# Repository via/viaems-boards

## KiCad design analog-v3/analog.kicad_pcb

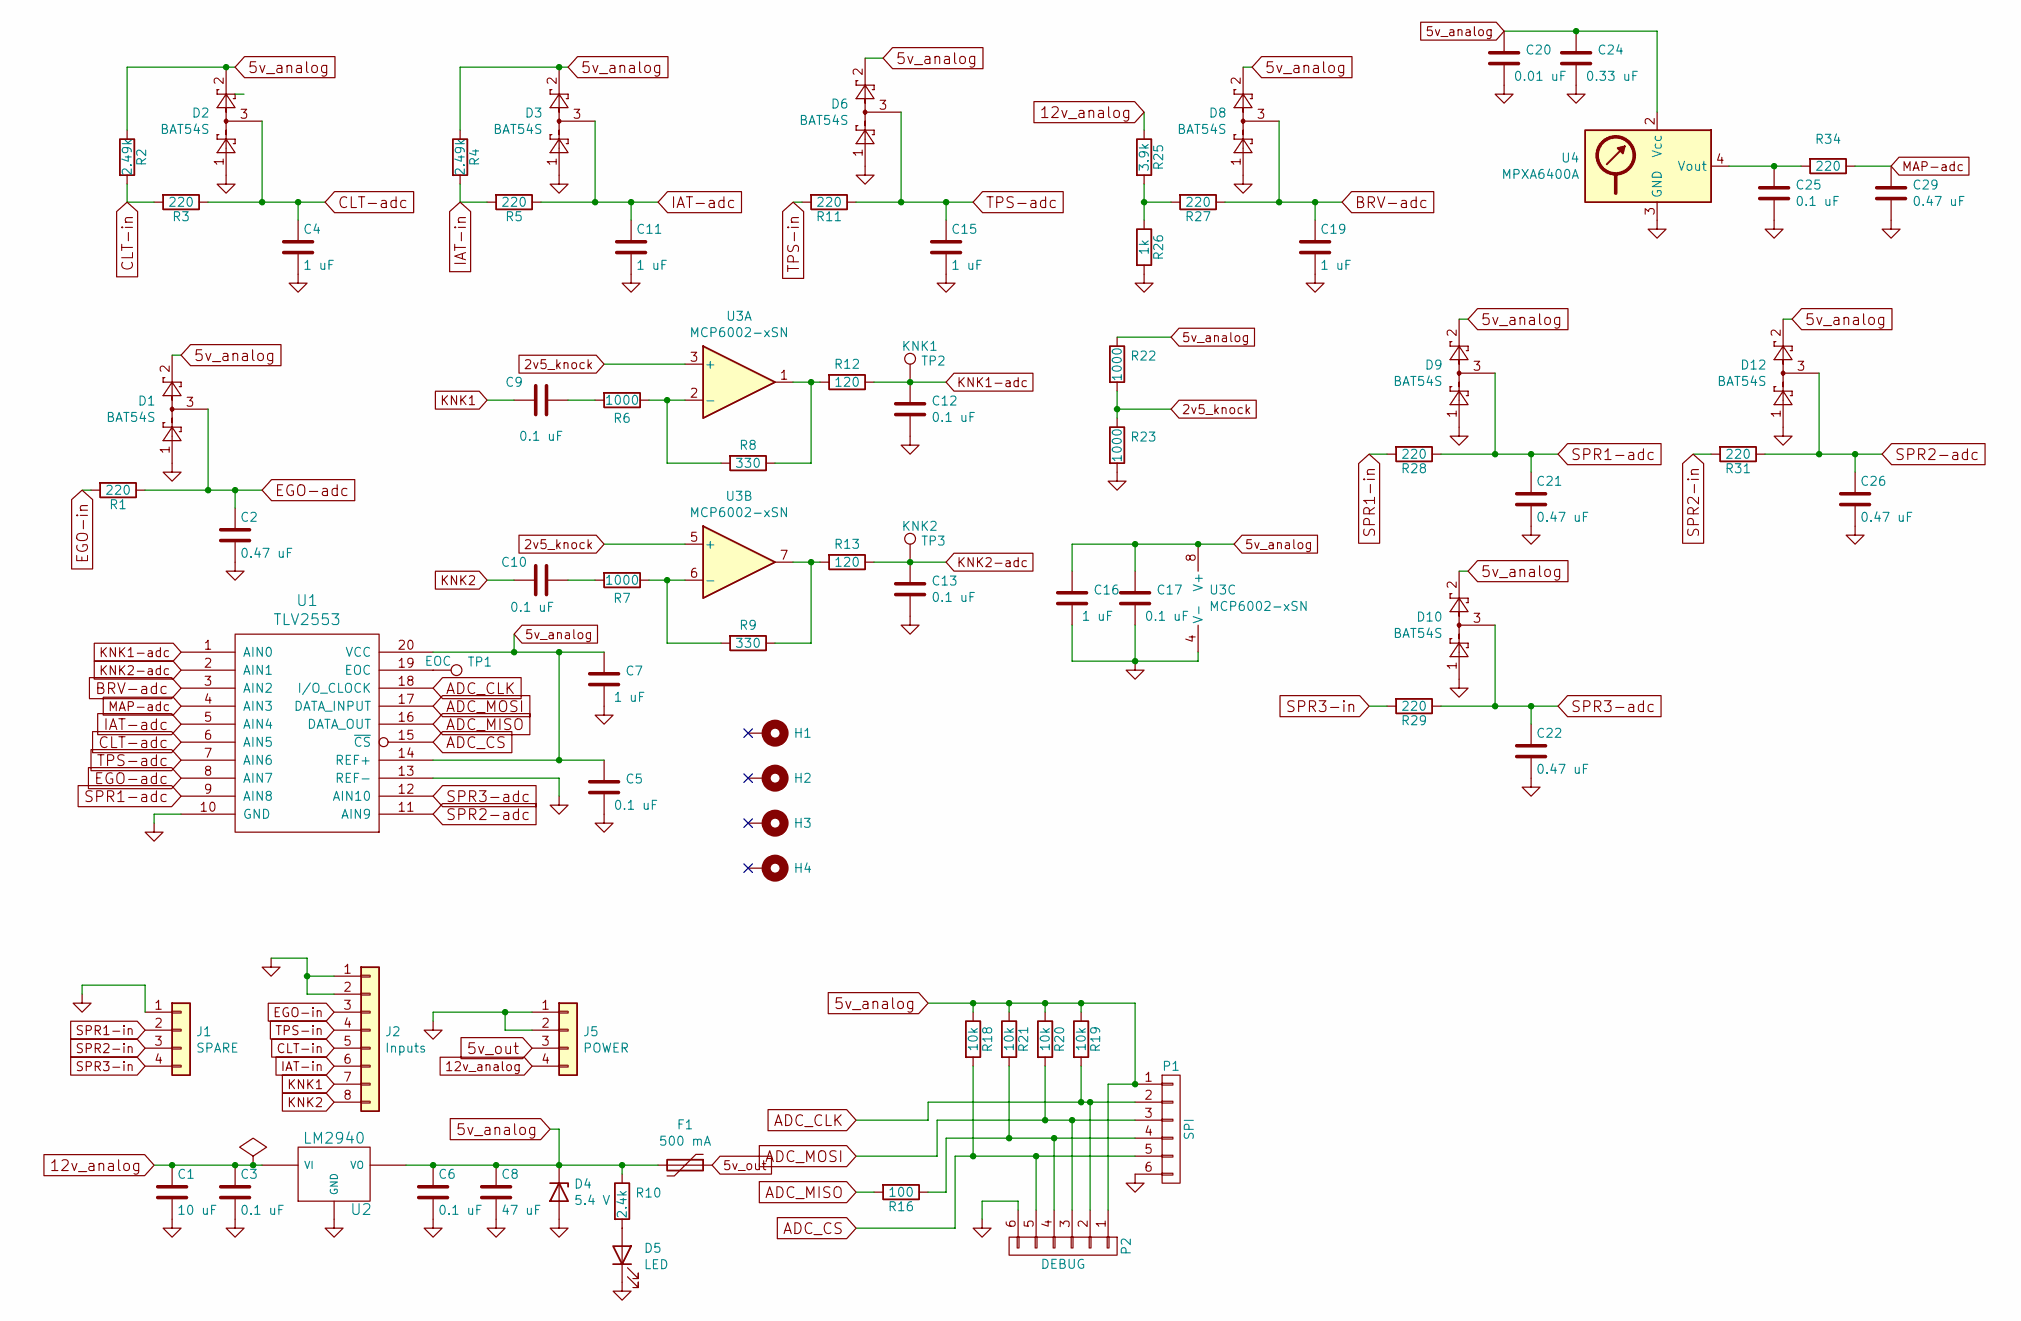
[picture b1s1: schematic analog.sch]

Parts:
C1: 10 uF; C_0805_2012Metric_Pad1.18x1.45mm_HandSolder; Rating 35V Tantalum
C2, C21, C22, C26, C29: 0.47 uF; C_0805_2012Metric_Pad1.18x1.45mm_HandSolder
C3, C5, C6, C9, C10, C12, C13, C17, C25: 0.1 uF; C_0805_2012Metric_Pad1.18x1.45mm_HandSolder
C4, C7, C11, C15, C16, C19: 1 uF; C_0805_2012Metric_Pad1.18x1.45mm_HandSolder
C8: 47 uF; C_1206_3216Metric_Pad1.33x1.80mm_HandSolder; Rating 10 V Tantalum
C20: 0.01 uF; C_0805_2012Metric_Pad1.18x1.45mm_HandSolder
C24: 0.33 uF; C_0805_2012Metric_Pad1.18x1.45mm_HandSolder
D1, D2, D3, D6, D8, D9, D10, D12: BAT54S; SOT-23
D4: 5.4 V; D_A-405_P2.54mm_Vertical_AnodeUp
D5: LED; LED_0805_2012Metric_Pad1.15x1.40mm_HandSolder
F1: 500 mA; Fuse_1206_3216Metric_Pad1.42x1.75mm_HandSolder
H1, H2, H3, H4: MountingHole_Pad; MountingHole_3mm_Pad
J1: SPARE; PinHeader_1x04_P2.54mm_Vertical
J2: Inputs; PinHeader_1x08_P2.54mm_Vertical
J5: POWER; PinHeader_1x04_P2.54mm_Vertical
P1: SPI; PinHeader_1x06_P2.54mm_Vertical
P2: DEBUG; PinHeader_1x06_P2.54mm_Vertical
R1, R3, R5, R11, R27, R28, R29, R31, R34: 220; R_0805_2012Metric_Pad1.20x1.40mm_HandSolder
R2, R4: 2.49k; R_0805_2012Metric_Pad1.20x1.40mm_HandSolder; Rating 0.1%
R6, R7, R22, R23: 1000; R_0805_2012Metric_Pad1.20x1.40mm_HandSolder
R8, R9: 330; R_0805_2012Metric_Pad1.20x1.40mm_HandSolder
R10: 2.4k; R_0805_2012Metric_Pad1.20x1.40mm_HandSolder
R12, R13: 120; R_0805_2012Metric_Pad1.20x1.40mm_HandSolder
R16: 100; R_0805_2012Metric_Pad1.20x1.40mm_HandSolder
R18, R19, R20, R21: 10k; R_0805_2012Metric_Pad1.20x1.40mm_HandSolder
R25: 3.9k; R_0805_2012Metric_Pad1.20x1.40mm_HandSolder; Rating 0.1%
R26: 1k; R_0805_2012Metric_Pad1.20x1.40mm_HandSolder; Rating 0.1%
TP1: EOC; TestPoint_THTPad_1.0x1.0mm_Drill0.5mm
TP2: KNK1; TestPoint_THTPad_1.0x1.0mm_Drill0.5mm
TP3: KNK2; TestPoint_THTPad_1.0x1.0mm_Drill0.5mm
U1: TLV2553; SOIC-20W_7.5x12.8mm_P1.27mm
U2: LM2940; TO-220-3_Horizontal_TabDown
U3: MCP6002-xSN; MSOP-8_3x3mm_P0.65mm
U4: MPXA6400A; Freescale_98ARH99089A

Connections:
2v5_knock: R22.2, R23.1, U3.3 (+), U3.5 (+)
5v_analog: C5.1, C6.1, C7.1, C8.1, C16.1, C17.1, C20.1, C24.1, D1.2, D2.2, D3.2, D4.1 (K), D6.2, D8.2, D9.2, D10.2, D12.2, F1.2, P1.1, P2.1, R2.1, R4.1, R10.1, R18.1, R19.1, R20.1, R21.1, R22.1, U1.14 (REF+), U1.20 (VCC), U2.3 (VO), U3.8 (V+), U4.2 (Vcc)
5v_out: F1.1, J5.3
12v_analog: C1.1, C3.1, J5.4, R25.1, U2.1 (VI)
ADC_CLK: P1.2, P2.2, R19.2, U1.18 (I/O_CLOCK)
ADC_CS: P1.5, P2.5, R18.2, U1.15 (~CS)
ADC_MISO: R16.2, U1.16 (DATA_OUT)
ADC_MOSI: P1.3, P2.3, R20.2, U1.17 (DATA_INPUT)
BRV-adc: C19.1, D8.3, R27.1, U1.3 (AIN2)
CLT-adc: C4.1, D2.3, R3.1, U1.6 (AIN5)
CLT-in: J2.5, R2.2, R3.2
EGO-adc: C2.1, D1.3, R1.1, U1.8 (AIN7)
EGO-in: J2.3, R1.2
GND: C1.2, C2.2, C3.2, C4.2, C5.2, C6.2, C7.2, C8.2, C11.2, C12.2, C13.2, C15.2, C16.2, C17.2, C19.2, C20.2, C21.2, C22.2, C24.2, C25.2, C26.2, C29.2, D1.1, D2.1, D3.1, D4.2 (A), D5.1 (K), D6.1, D8.1, D9.1, D10.1, D12.1, J1.1, J2.1, J2.2, J5.1, J5.2, P1.6, P2.6, R23.2, R26.2, U1.10 (GND), U1.13 (REF-), U2.2 (GND), U3.4 (V-), U4.3 (GND)
IAT-adc: C11.1, D3.3, R5.1, U1.5 (AIN4)
IAT-in: J2.6, R4.2, R5.2
KNK1: C9.2, J2.7
KNK1-adc: C12.1, R12.1, TP2.1, U1.1 (AIN0)
KNK2: C10.2, J2.8
KNK2-adc: C13.1, R13.1, TP3.1, U1.2 (AIN1)
MAP-adc: C29.1, R34.1, U1.4 (AIN3)
unnamed: C9.1, R6.2
unnamed: C10.1, R7.2
unnamed: C25.1, R34.2, U4.4 (Vout)
unnamed: D5.2 (A), R10.2
unnamed: P1.4, P2.4, R16.1, R21.2
unnamed: R6.1, R8.2, U3.2 (-)
unnamed: R7.1, R9.2, U3.6 (-)
unnamed: R8.1, R12.2, U3.1
unnamed: R9.1, R13.2, U3.7
unnamed: R25.2, R26.1, R27.2
unnamed: TP1.1, U1.19 (EOC)
SPR1-adc: C21.1, D9.3, R28.1, U1.9 (AIN8)
SPR1-in: J1.2, R28.2
SPR2-adc: C26.1, D12.3, R31.1, U1.11 (AIN9)
SPR2-in: J1.3, R31.2
SPR3-adc: C22.1, D10.3, R29.1, U1.12 (AIN10)
SPR3-in: J1.4, R29.2
TPS-adc: C15.1, D6.3, R11.1, U1.7 (AIN6)
TPS-in: J2.4, R11.2

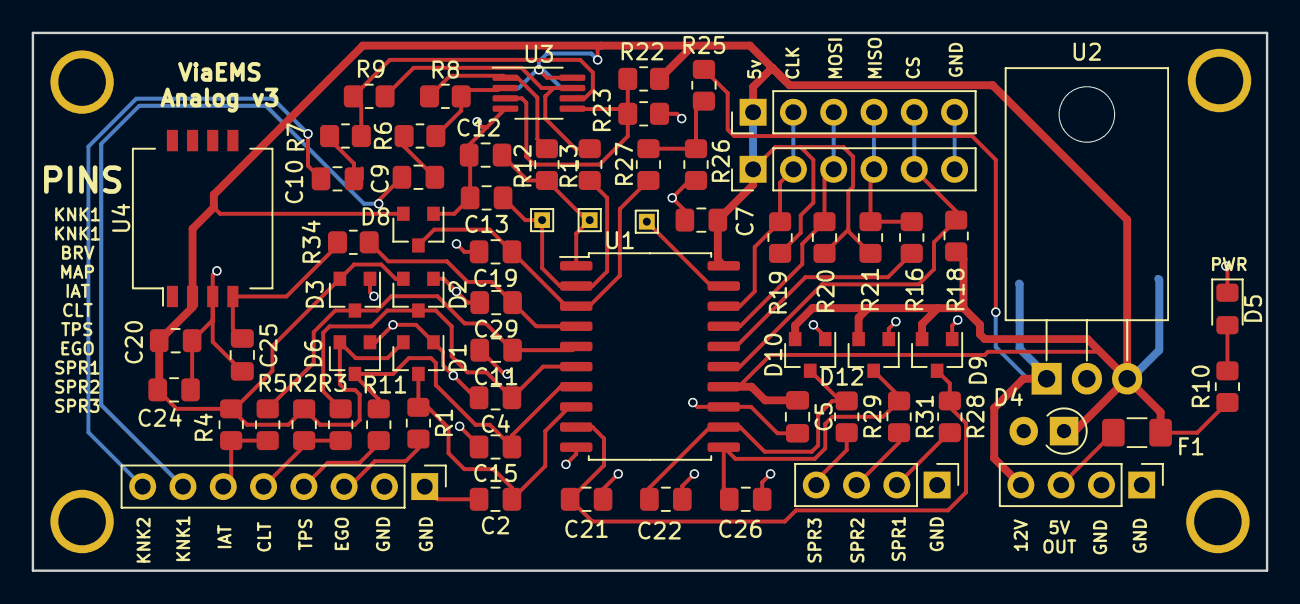
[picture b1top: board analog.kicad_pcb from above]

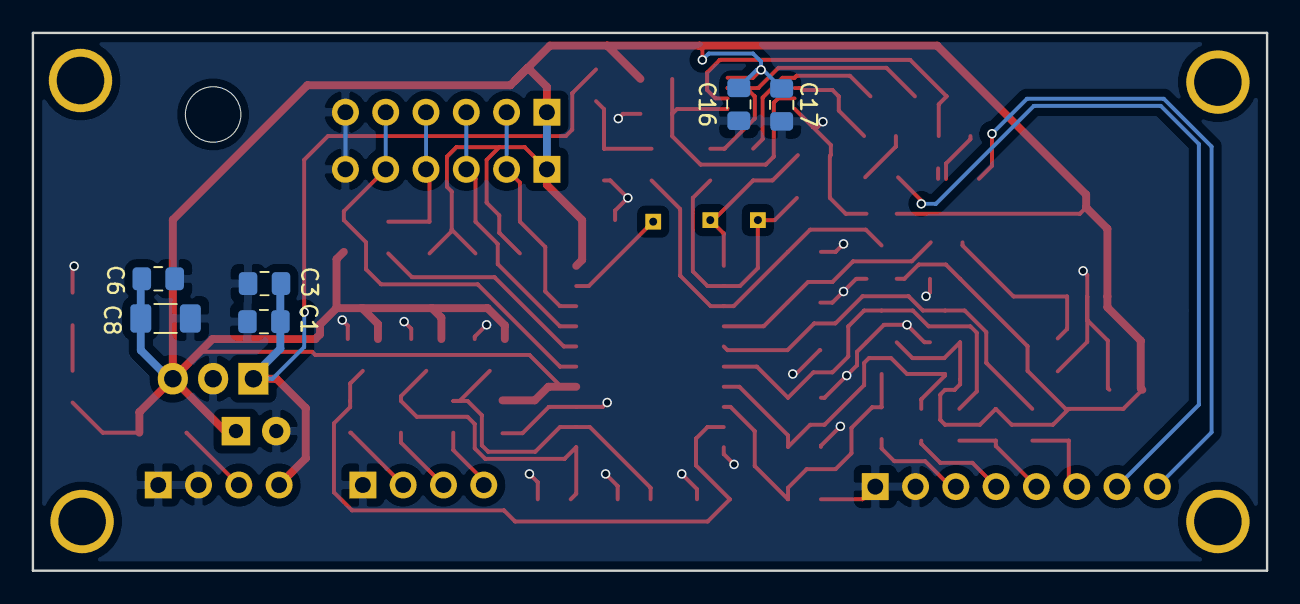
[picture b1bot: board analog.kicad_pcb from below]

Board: 2 copper layers, 77.8 x 33.9 mm, 78 parts (6 on the bottom side), 40 nets.

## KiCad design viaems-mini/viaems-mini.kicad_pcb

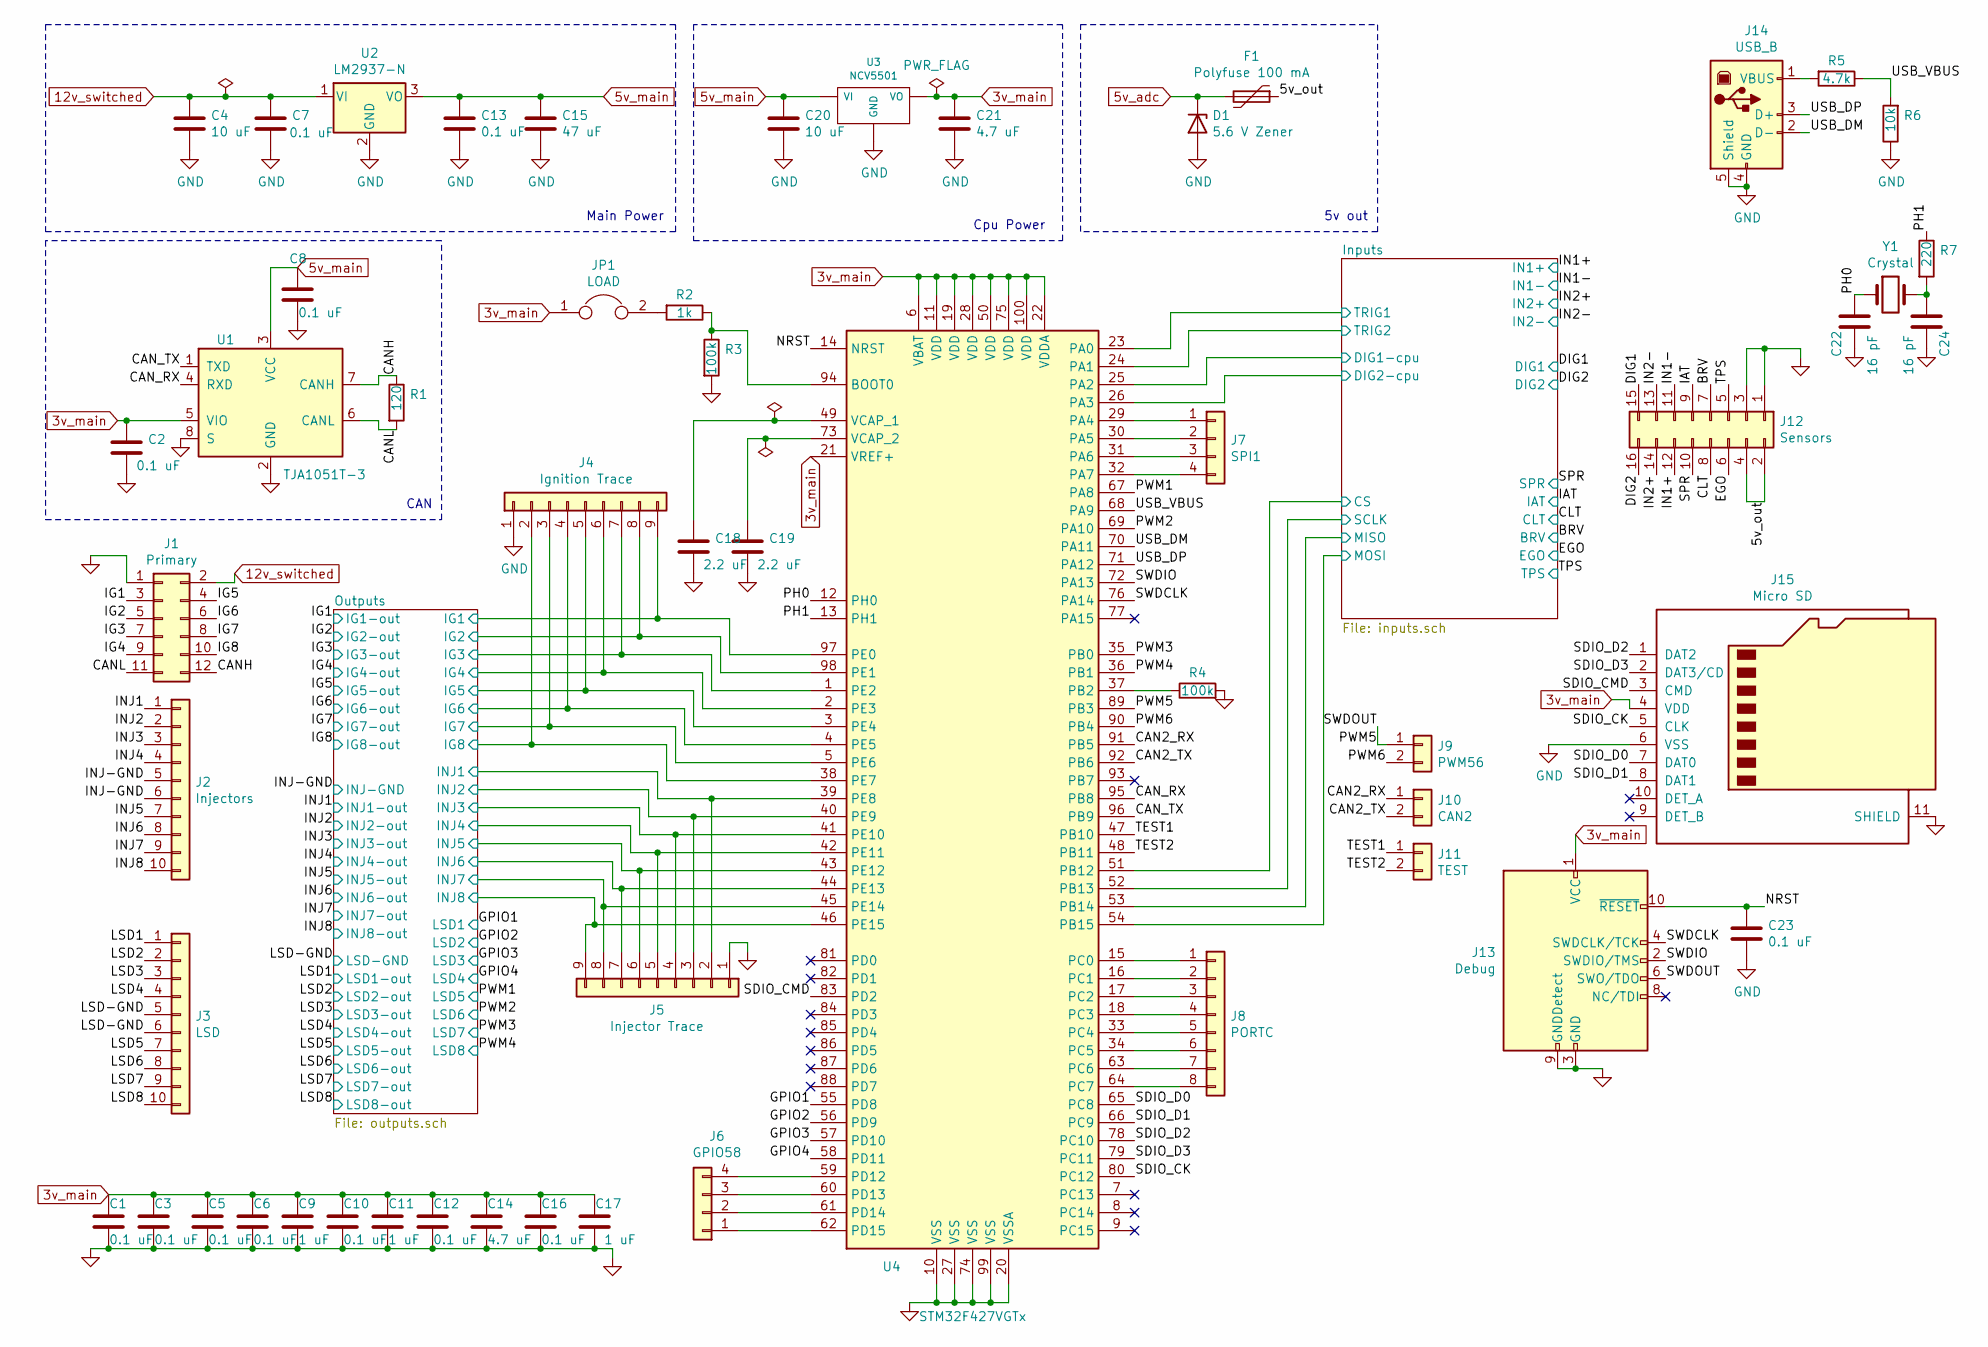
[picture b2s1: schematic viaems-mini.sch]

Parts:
C1, C2, C3, C5, C6, C7, C8, C10, C12, C13, C16, C23: 0.1 uF; C_0805_2012Metric
C4, C20: 10 uF; C_0805_2012Metric
C9, C11, C17: 1 uF; C_0805_2012Metric
C14, C21: 4.7 uF; C_0805_2012Metric
C15: 47 uF; C_1206_3216Metric; Digikey-Part 478-9009-1-ND
C18, C19: 2.2 uF; C_0805_2012Metric
C22, C24: 16 pF; C_0805_2012Metric
D1: 5.6 V Zener; D_DO-41_SOD81_P2.54mm_Vertical_AnodeUp
F1: Polyfuse 100 mA; Fuse_0805_2012Metric; Digikey-Part 283-PTS080524V010CT-ND
J1: Primary; PinHeader_2x06_P2.54mm_Vertical
J2: Injectors; PinHeader_1x10_P2.54mm_Vertical
J3: LSD; PinHeader_1x10_P2.54mm_Vertical
J4: Ignition Trace; PinHeader_1x09_P2.54mm_Vertical
J5: Injector Trace; PinHeader_1x09_P2.54mm_Vertical
J6: GPIO58; PinHeader_1x04_P2.54mm_Vertical
J7: SPI1; PinHeader_1x04_P2.54mm_Vertical
J8: PORTC; PinHeader_1x08_P2.54mm_Vertical
J9: PWM56; PinHeader_1x02_P2.54mm_Vertical
J10: CAN2; PinHeader_1x02_P2.54mm_Vertical
J11: TEST; PinHeader_1x02_P2.54mm_Vertical
J12: Sensors; PinHeader_2x08_P2.54mm_Vertical
J13: Debug; PinHeader_2x05_P1.27mm_Vertical_SMD; Digikey-Part SAM9438-ND
J14: USB_B; USB_B_OST_USB-B1HSxx_Horizontal; Digikey-Part ED2982-ND
J15: Micro SD; microSD_HC_Hirose_DM3D-SF
JP1: LOAD; PinHeader_1x02_P2.54mm_Vertical
R1: 120; R_0805_2012Metric
R2: 1k; R_0805_2012Metric
R3, R4: 100k; R_0805_2012Metric
R5: 4.7k; R_0805_2012Metric
R6: 10k; R_0805_2012Metric
R7: 220; R_0805_2012Metric
U1: TJA1051T-3; SOIC-8_3.9x4.9mm_P1.27mm
U2: LM2937-N; TO-220-3_Horizontal_TabDown
U3: NCV5501; TO-263-2
U4: STM32F427VGTx; LQFP-100_14x14mm_P0.5mm
Y1: Crystal; Crystal_HC49-U_Vertical

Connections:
3v_main: C1.1, C2.1, C3.1, C5.1, C6.1, C9.1, C10.1, C11.1, C12.1, C14.1, C16.1, C17.1, C21.1, J13.1 (VCC), J15.4 (VDD), JP1.1, U1.5 (VIO), U3.3 (VO), U4.6 (VBAT), U4.11 (VDD), U4.19 (VDD), U4.21 (VREF+), U4.22 (VDDA), U4.28 (VDD), U4.50 (VDD), U4.75 (VDD), U4.100 (VDD)
5v_adc: D1.1 (K), F1.2; also elsewhere on the board
5v_main: C8.1, C13.1, C15.1, C20.1, U1.3 (VCC), U2.3 (VO), U3.1 (VI); also elsewhere on the board
12v_switched: C4.1, C7.1, J1.2, U2.1 (VI); also elsewhere on the board
/5v_out: F1.1, J12.2, J12.4
/BRV: J12.7; also elsewhere on the board
/CAN2_RX: J10.1, U4.91 (PB5)
/CAN2_TX: J10.2, U4.92 (PB6)
/CANH: J1.12, R1.1, U1.7 (CANH)
/CANL: J1.11, R1.2, U1.6 (CANL)
/CAN_RX: U1.4 (RXD), U4.95 (PB8)
/CAN_TX: U1.1 (TXD), U4.96 (PB9)
/CLT: J12.8; also elsewhere on the board
/DIG1: J12.15; also elsewhere on the board
/DIG2: J12.16; also elsewhere on the board
/EGO: J12.6; also elsewhere on the board
/GPIO1: U4.55 (PD8); also elsewhere on the board
/GPIO2: U4.56 (PD9); also elsewhere on the board
/GPIO3: U4.57 (PD10); also elsewhere on the board
/GPIO4: U4.58 (PD11); also elsewhere on the board
/IAT: J12.9; also elsewhere on the board
/IG1: J1.3; also elsewhere on the board
/IG2: J1.5; also elsewhere on the board
/IG3: J1.7; also elsewhere on the board
/IG4: J1.9; also elsewhere on the board
/IG5: J1.4; also elsewhere on the board
/IG6: J1.6; also elsewhere on the board
/IG7: J1.8; also elsewhere on the board
/IG8: J1.10; also elsewhere on the board
/IN1+: J12.12; also elsewhere on the board
/IN1-: J12.11; also elsewhere on the board
/IN2+: J12.14; also elsewhere on the board
/IN2-: J12.13; also elsewhere on the board
/INJ1: J2.1; also elsewhere on the board
/INJ2: J2.2; also elsewhere on the board
/INJ3: J2.3; also elsewhere on the board
/INJ4: J2.4; also elsewhere on the board
/INJ5: J2.7; also elsewhere on the board
/INJ6: J2.8; also elsewhere on the board
/INJ7: J2.9; also elsewhere on the board
/INJ8: J2.10; also elsewhere on the board
/INJ-GND: J2.5, J2.6; also elsewhere on the board
/Inputs/CS: U4.51 (PB12); also elsewhere on the board
/Inputs/DIG1-cpu: U4.25 (PA2); also elsewhere on the board
/Inputs/DIG2-cpu: U4.26 (PA3); also elsewhere on the board
/Inputs/MISO: U4.53 (PB14); also elsewhere on the board
/Inputs/MOSI: U4.54 (PB15); also elsewhere on the board
/Inputs/SCLK: U4.52 (PB13); also elsewhere on the board
/Inputs/TRIG1: U4.23 (PA0); also elsewhere on the board
/Inputs/TRIG2: U4.24 (PA1); also elsewhere on the board
/LSD1: J3.1; also elsewhere on the board
/LSD2: J3.2; also elsewhere on the board
/LSD3: J3.3; also elsewhere on the board
/LSD4: J3.4; also elsewhere on the board
/LSD5: J3.7; also elsewhere on the board
/LSD6: J3.8; also elsewhere on the board
/LSD7: J3.9; also elsewhere on the board
/LSD8: J3.10; also elsewhere on the board
/LSD-GND: J3.5, J3.6; also elsewhere on the board
/NRST: C23.1, J13.10 (~RESET~), U4.14 (NRST)
/Outputs/IG1: J4.9, U4.97 (PE0); also elsewhere on the board
/Outputs/IG2: J4.8, U4.98 (PE1); also elsewhere on the board
/Outputs/IG3: J4.7, U4.1 (PE2); also elsewhere on the board
/Outputs/IG4: J4.6, U4.2 (PE3); also elsewhere on the board
/Outputs/IG5: J4.5, U4.3 (PE4); also elsewhere on the board
/Outputs/IG6: J4.4, U4.4 (PE5); also elsewhere on the board
/Outputs/IG7: J4.3, U4.5 (PE6); also elsewhere on the board
/Outputs/IG8: J4.2, U4.38 (PE7); also elsewhere on the board
/Outputs/INJ1: J5.2, U4.39 (PE8); also elsewhere on the board
/Outputs/INJ2: J5.3, U4.40 (PE9); also elsewhere on the board
/Outputs/INJ3: J5.4, U4.41 (PE10); also elsewhere on the board
/Outputs/INJ4: J5.5, U4.42 (PE11); also elsewhere on the board
/Outputs/INJ5: J5.6, U4.43 (PE12); also elsewhere on the board
/Outputs/INJ6: J5.7, U4.44 (PE13); also elsewhere on the board
/Outputs/INJ7: J5.8, U4.45 (PE14); also elsewhere on the board
/Outputs/INJ8: J5.9, U4.46 (PE15); also elsewhere on the board
/PH0: C22.1, U4.12 (PH0), Y1.1
/PH1: R7.1, U4.13 (PH1)
/PWM1: U4.67 (PA8); also elsewhere on the board
/PWM2: U4.69 (PA10); also elsewhere on the board
/PWM3: U4.35 (PB0); also elsewhere on the board
/PWM4: U4.36 (PB1); also elsewhere on the board
/PWM5: J9.1, J13.6 (SWO/TDO), U4.89 (PB3)
/PWM6: J9.2, U4.90 (PB4)
/SDIO_CK: J15.5 (CLK), U4.80 (PC12)
/SDIO_CMD: J15.3 (CMD), U4.83 (PD2)
/SDIO_D0: J15.7 (DAT0), U4.65 (PC8)
/SDIO_D1: J15.8 (DAT1), U4.66 (PC9)
/SDIO_D2: J15.1 (DAT2), U4.78 (PC10)
/SDIO_D3: J15.2 (DAT3/CD), U4.79 (PC11)
/SPR: J12.10; also elsewhere on the board
/SWDCLK: J13.4 (SWDCLK/TCK), U4.76 (PA14)
/SWDIO: J13.2 (SWDIO/TMS), U4.72 (PA13)
/TEST1: J11.1, U4.47 (PB10)
/TEST2: J11.2, U4.48 (PB11)
/TPS: J12.5; also elsewhere on the board
/USB_DM: J14.2 (D-), U4.70 (PA11)
/USB_DP: J14.3 (D+), U4.71 (PA12)
/USB_VBUS: R5.1, R6.2, U4.68 (PA9)
GND: C1.2, C2.2, C3.2, C4.2, C5.2, C6.2, C7.2, C8.2, C9.2, C10.2, C11.2, C12.2, C13.2, C14.2, C15.2, C16.2, C17.2, C18.2, C19.2, C20.2, C21.2, C22.2, C23.2, C24.2, D1.2 (A), J1.1, J4.1, J5.1, J12.1, J12.3, J13.3 (GND), J13.5 (GND), J13.9 (GNDDetect), J14.4 (GND), J14.5 (Shield), J15.6 (VSS), J15.11 (SHIELD), R3.2, R4.2, R6.1, U1.2 (GND), U1.8 (S), U2.2 (GND), U3.2 (GND), U4.10 (VSS), U4.20 (VSSA), U4.27 (VSS), U4.74 (VSS), U4.99 (VSS); also elsewhere on the board
unnamed: C18.1, U4.49 (VCAP_1)
unnamed: C19.1, U4.73 (VCAP_2)
unnamed: C24.1, R7.2, Y1.2
unnamed: J6.1, U4.62 (PD15)
unnamed: J6.2, U4.61 (PD14)
unnamed: J6.3, U4.60 (PD13)
unnamed: J6.4, U4.59 (PD12)
unnamed: J7.1, U4.29 (PA4)
unnamed: J7.2, U4.30 (PA5)
unnamed: J7.3, U4.31 (PA6)
unnamed: J7.4, U4.32 (PA7)
unnamed: J8.1, U4.15 (PC0)
unnamed: J8.2, U4.16 (PC1)
unnamed: J8.3, U4.17 (PC2)
unnamed: J8.4, U4.18 (PC3)
unnamed: J8.5, U4.33 (PC4)
unnamed: J8.6, U4.34 (PC5)
unnamed: J8.7, U4.63 (PC6)
unnamed: J8.8, U4.64 (PC7)
unnamed: J14.1 (VBUS), R5.2
unnamed: JP1.2, R2.2
unnamed: R2.1, R3.1, U4.94 (BOOT0)
unnamed: R4.1, U4.37 (PB2)

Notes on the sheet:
Main Power
Cpu Power
CAN
5v out

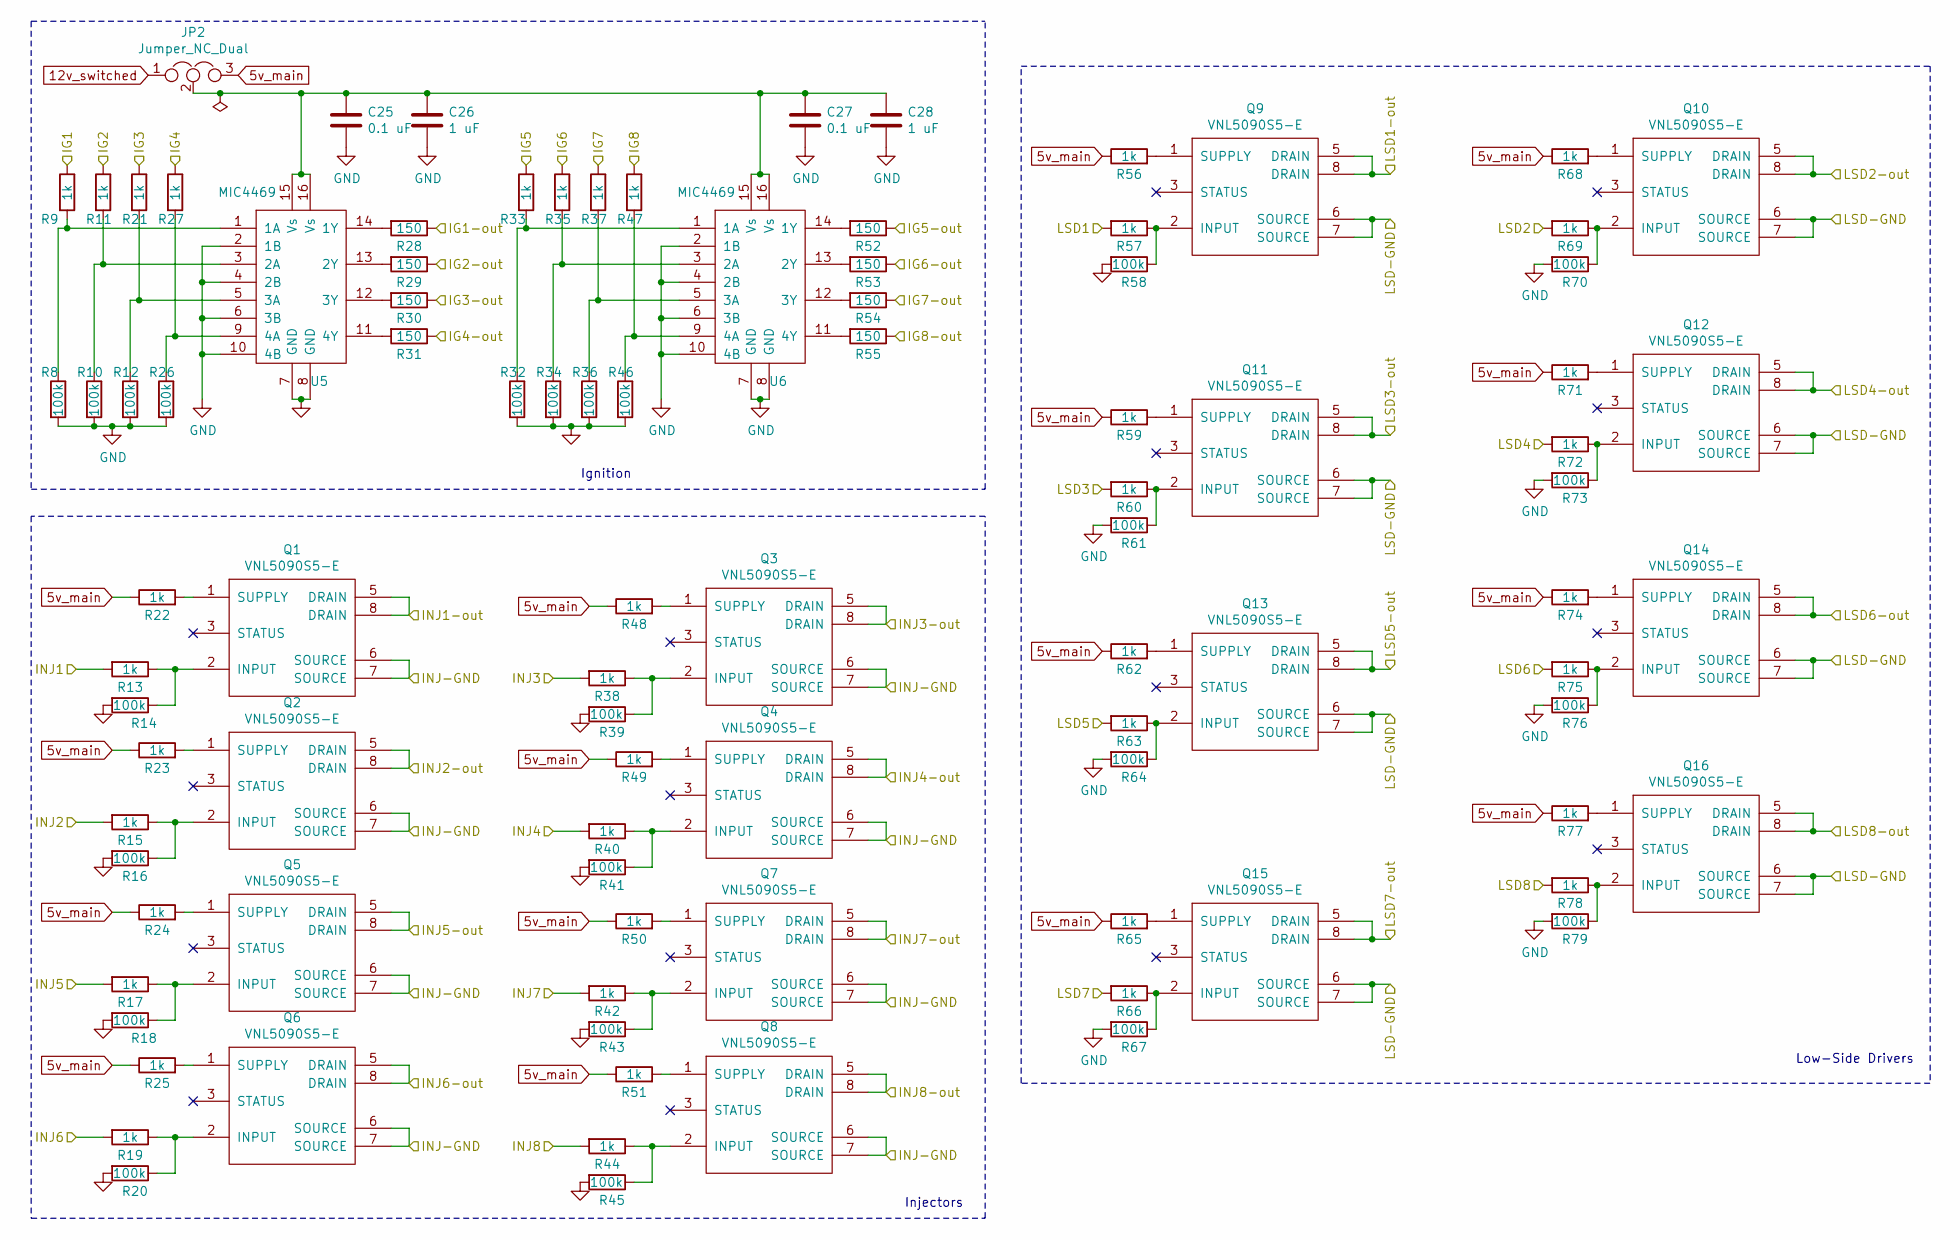
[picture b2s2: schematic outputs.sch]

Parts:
C25, C27: 0.1 uF; C_0805_2012Metric
C26, C28: 1 uF; C_0805_2012Metric
JP2: Jumper_NC_Dual; PinHeader_1x03_P2.54mm_Vertical
Q1, Q2, Q3, Q4, Q5, Q6, Q7, Q8, Q9, Q10, Q11, Q12, Q13, Q14, Q15, Q16: VNL5090S5-E; SO-8_5.3x6.2mm_P1.27mm
R8, R10, R12, R14, R16, R18, R20, R26, R32, R34, R36, R39, R41, R43, R45, R46, R58, R61, R64, R67, R70, R73, R76, R79: 100k; R_0805_2012Metric
R9, R11, R13, R15, R17, R19, R21, R22, R23, R24, R25, R27, R33, R35, R37, R38, R40, R42, R44, R47, R48, R49, R50, R51, R56, R57, R59, R60, R62, R63, R65, R66, R68, R69, R71, R72, R74, R75, R77, R78: 1k; R_0805_2012Metric
R28, R29, R30, R31, R52, R53, R54, R55: 150; R_0805_2012Metric
U5, U6: MIC4469; SOIC-16W_7.5x10.3mm_P1.27mm; Part MIC4469BWM

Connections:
5v_main: JP2.3, R22.1, R23.1, R24.1, R25.1, R48.1, R49.1, R50.1, R51.1, R56.1, R59.1, R62.1, R65.1, R68.1, R71.1, R74.1, R77.1; also elsewhere on the board
12v_switched: JP2.1; also elsewhere on the board
/GPIO1: R57.2; also elsewhere on the board
/GPIO2: R69.2; also elsewhere on the board
/GPIO3: R60.2; also elsewhere on the board
/GPIO4: R72.2; also elsewhere on the board
/IG1: R28.1; also elsewhere on the board
/IG2: R29.1; also elsewhere on the board
/IG3: R30.1; also elsewhere on the board
/IG4: R31.1; also elsewhere on the board
/IG5: R52.1; also elsewhere on the board
/IG6: R53.1; also elsewhere on the board
/IG7: R54.1; also elsewhere on the board
/IG8: R55.1; also elsewhere on the board
/INJ1: Q1.5 (DRAIN), Q1.8 (DRAIN); also elsewhere on the board
/INJ2: Q2.5 (DRAIN), Q2.8 (DRAIN); also elsewhere on the board
/INJ3: Q3.5 (DRAIN), Q3.8 (DRAIN); also elsewhere on the board
/INJ4: Q4.5 (DRAIN), Q4.8 (DRAIN); also elsewhere on the board
/INJ5: Q5.5 (DRAIN), Q5.8 (DRAIN); also elsewhere on the board
/INJ6: Q6.5 (DRAIN), Q6.8 (DRAIN); also elsewhere on the board
/INJ7: Q7.5 (DRAIN), Q7.8 (DRAIN); also elsewhere on the board
/INJ8: Q8.5 (DRAIN), Q8.8 (DRAIN); also elsewhere on the board
/INJ-GND: Q1.6 (SOURCE), Q1.7 (SOURCE), Q2.6 (SOURCE), Q2.7 (SOURCE), Q3.6 (SOURCE), Q3.7 (SOURCE), Q4.6 (SOURCE), Q4.7 (SOURCE), Q5.6 (SOURCE), Q5.7 (SOURCE), Q6.6 (SOURCE), Q6.7 (SOURCE), Q7.6 (SOURCE), Q7.7 (SOURCE), Q8.6 (SOURCE), Q8.7 (SOURCE); also elsewhere on the board
/LSD1: Q9.5 (DRAIN), Q9.8 (DRAIN); also elsewhere on the board
/LSD2: Q10.5 (DRAIN), Q10.8 (DRAIN); also elsewhere on the board
/LSD3: Q11.5 (DRAIN), Q11.8 (DRAIN); also elsewhere on the board
/LSD4: Q12.5 (DRAIN), Q12.8 (DRAIN); also elsewhere on the board
/LSD5: Q13.5 (DRAIN), Q13.8 (DRAIN); also elsewhere on the board
/LSD6: Q14.5 (DRAIN), Q14.8 (DRAIN); also elsewhere on the board
/LSD7: Q15.5 (DRAIN), Q15.8 (DRAIN); also elsewhere on the board
/LSD8: Q16.5 (DRAIN), Q16.8 (DRAIN); also elsewhere on the board
/LSD-GND: Q9.6 (SOURCE), Q9.7 (SOURCE), Q10.6 (SOURCE), Q10.7 (SOURCE), Q11.6 (SOURCE), Q11.7 (SOURCE), Q12.6 (SOURCE), Q12.7 (SOURCE), Q13.6 (SOURCE), Q13.7 (SOURCE), Q14.6 (SOURCE), Q14.7 (SOURCE), Q15.6 (SOURCE), Q15.7 (SOURCE), Q16.6 (SOURCE), Q16.7 (SOURCE); also elsewhere on the board
/Outputs/IG1: R9.1; also elsewhere on the board
/Outputs/IG2: R11.1; also elsewhere on the board
/Outputs/IG3: R21.1; also elsewhere on the board
/Outputs/IG4: R27.1; also elsewhere on the board
/Outputs/IG5: R33.1; also elsewhere on the board
/Outputs/IG6: R35.1; also elsewhere on the board
/Outputs/IG7: R37.1; also elsewhere on the board
/Outputs/IG8: R47.1; also elsewhere on the board
/Outputs/INJ1: R13.2; also elsewhere on the board
/Outputs/INJ2: R15.2; also elsewhere on the board
/Outputs/INJ3: R38.2; also elsewhere on the board
/Outputs/INJ4: R40.2; also elsewhere on the board
/Outputs/INJ5: R17.2; also elsewhere on the board
/Outputs/INJ6: R19.2; also elsewhere on the board
/Outputs/INJ7: R42.2; also elsewhere on the board
/Outputs/INJ8: R44.2; also elsewhere on the board
/PWM1: R63.2; also elsewhere on the board
/PWM2: R75.2; also elsewhere on the board
/PWM3: R66.2; also elsewhere on the board
/PWM4: R78.2; also elsewhere on the board
GND: C25.2, C26.2, C27.2, C28.2, R8.2, R10.2, R12.2, R14.2, R16.2, R18.2, R20.2, R26.2, R32.2, R34.2, R36.2, R39.2, R41.2, R43.2, R45.2, R46.2, R58.2, R61.2, R64.2, R67.2, R70.2, R73.2, R76.2, R79.2, U5.2 (1B), U5.4 (2B), U5.6 (3B), U5.7 (GND), U5.8 (GND), U5.10 (4B), U6.2 (1B), U6.4 (2B), U6.6 (3B), U6.7 (GND), U6.8 (GND), U6.10 (4B); also elsewhere on the board
unnamed: C25.1, C26.1, C27.1, C28.1, JP2.2, U5.15 (Vs), U5.16 (Vs), U6.15 (Vs), U6.16 (Vs)
unnamed: Q1.1 (SUPPLY), R22.2
unnamed: Q1.2 (INPUT), R13.1, R14.1
unnamed: Q2.1 (SUPPLY), R23.2
unnamed: Q2.2 (INPUT), R15.1, R16.1
unnamed: Q3.1 (SUPPLY), R48.2
unnamed: Q3.2 (INPUT), R38.1, R39.1
unnamed: Q4.1 (SUPPLY), R49.2
unnamed: Q4.2 (INPUT), R40.1, R41.1
unnamed: Q5.1 (SUPPLY), R24.2
unnamed: Q5.2 (INPUT), R17.1, R18.1
unnamed: Q6.1 (SUPPLY), R25.2
unnamed: Q6.2 (INPUT), R19.1, R20.1
unnamed: Q7.1 (SUPPLY), R50.2
unnamed: Q7.2 (INPUT), R42.1, R43.1
unnamed: Q8.1 (SUPPLY), R51.2
unnamed: Q8.2 (INPUT), R44.1, R45.1
unnamed: Q9.1 (SUPPLY), R56.2
unnamed: Q9.2 (INPUT), R57.1, R58.1
unnamed: Q10.1 (SUPPLY), R68.2
unnamed: Q10.2 (INPUT), R69.1, R70.1
unnamed: Q11.1 (SUPPLY), R59.2
unnamed: Q11.2 (INPUT), R60.1, R61.1
unnamed: Q12.1 (SUPPLY), R71.2
unnamed: Q12.2 (INPUT), R72.1, R73.1
unnamed: Q13.1 (SUPPLY), R62.2
unnamed: Q13.2 (INPUT), R63.1, R64.1
unnamed: Q14.1 (SUPPLY), R74.2
unnamed: Q14.2 (INPUT), R75.1, R76.1
unnamed: Q15.1 (SUPPLY), R65.2
unnamed: Q15.2 (INPUT), R66.1, R67.1
unnamed: Q16.1 (SUPPLY), R77.2
unnamed: Q16.2 (INPUT), R78.1, R79.1
unnamed: R8.1, R9.2, U5.1 (1A)
unnamed: R10.1, R11.2, U5.3 (2A)
unnamed: R12.1, R21.2, U5.5 (3A)
unnamed: R26.1, R27.2, U5.9 (4A)
unnamed: R28.2, U5.14 (1Y)
unnamed: R29.2, U5.13 (2Y)
unnamed: R30.2, U5.12 (3Y)
unnamed: R31.2, U5.11 (4Y)
unnamed: R32.1, R33.2, U6.1 (1A)
unnamed: R34.1, R35.2, U6.3 (2A)
unnamed: R36.1, R37.2, U6.5 (3A)
unnamed: R46.1, R47.2, U6.9 (4A)
unnamed: R52.2, U6.14 (1Y)
unnamed: R53.2, U6.13 (2Y)
unnamed: R54.2, U6.12 (3Y)
unnamed: R55.2, U6.11 (4Y)

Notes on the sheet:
Ignition
Injectors
Low-Side Drivers
